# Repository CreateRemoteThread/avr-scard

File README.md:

# avr-scard

this is an extremely minimal t0 iso7816 reader based off an atmega328p, communicating over serial at 9600 baud.

this implements a fixed wait after 5 bytes of APDU, but otherwise does not guarantee reponses for APDU's. the pyserial driver is currently a part of [sparkgap](https://github.com/createremotethread/sparkgap). The pin out is as follows:

- B4: Status LED
- B0: Target I/O
- B2: Target Reset
- B1: Target Clk
- C5: Trigger (after APDU Send)

this is based off https://www.makomk.com/2011/02/25/iso-7816-smartcard-interface-for-arduino/

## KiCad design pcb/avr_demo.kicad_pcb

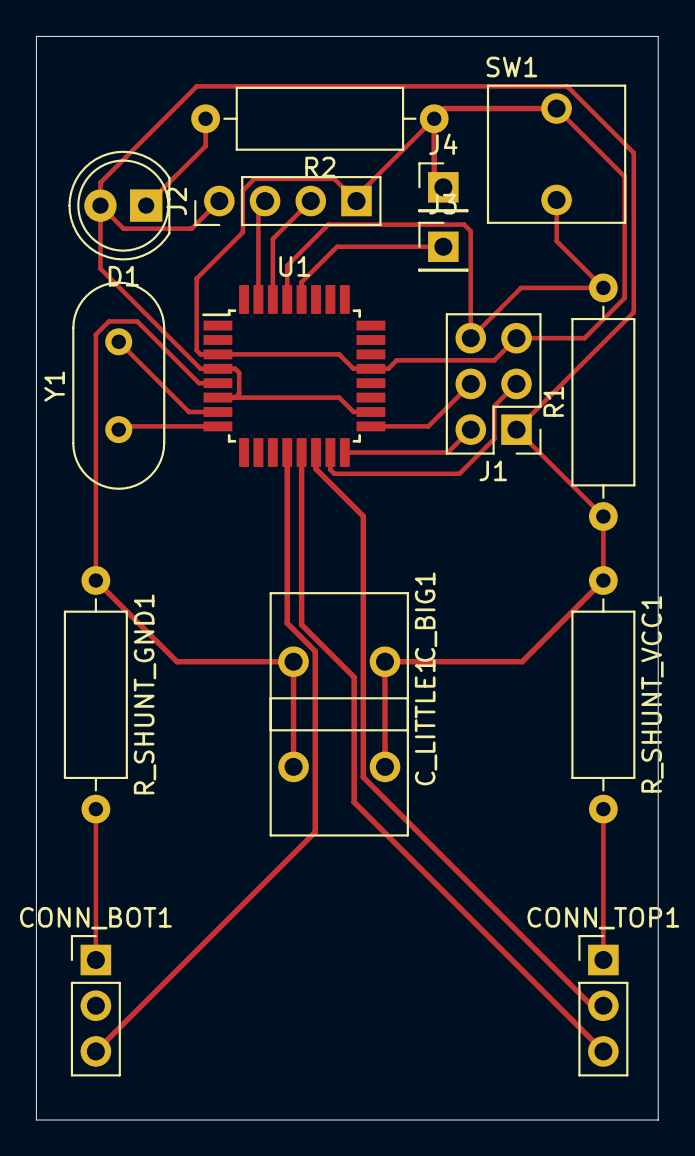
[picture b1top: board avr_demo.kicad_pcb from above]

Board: 2 copper layers, 34.5 x 60.2 mm, 16 parts (0 on the bottom side), 17 nets.

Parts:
CONN_BOT1: Conn_01x03; PinHeader_1x03_P2.54mm_Vertical
CONN_TOP1: Conn_01x03; PinHeader_1x03_P2.54mm_Vertical
C_BIG1: C; SW_6x6
C_LITTLE1: C; SW_6x6
D1: LED; LED_D5.0mm
J1: AVR-ISP-6; AVRISP_2x3
J2: Conn_01x04; PinHeader_1x04_P2.54mm_Vertical
J3, J4: Conn_01x01_Male; PinHeader_1x01_P2.54mm_Vertical
R1, R2: R; R_Axial_DIN0309_L9.0mm_D3.2mm_P12.70mm_Horizontal
R_SHUNT_GND1: R; R_Axial_DIN0309_L9.0mm_D3.2mm_P12.70mm_Horizontal
R_SHUNT_VCC1: R; R_Axial_DIN0309_L9.0mm_D3.2mm_P12.70mm_Horizontal
SW1: SW_Push; SW_6x6
U1: ATmega328P-AU; TQFP-32_7x7mm_P0.8mm
Y1: Crystal; Crystal_HC49-4H_Vertical

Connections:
GND: C_BIG1.2, C_LITTLE1.2, J1.6, J2.4, J4.1, R2.1, R_SHUNT_GND1.1, SW1.1, U1.3, U1.5, U1.21
ISP_MISO: J1.1, U1.16
ISP_MOSI: J1.4, U1.15
ISP_RST: J1.5, R1.2, SW1.2, U1.29
ISP_SCK: J1.3, U1.17
unnamed: CONN_BOT1.1, R_SHUNT_GND1.2
unnamed: CONN_TOP1.1, R_SHUNT_VCC1.2
unnamed: D1.1, R2.2
unnamed: U1.7, Y1.2
unnamed: U1.8, Y1.1
SC_CLK: CONN_TOP1.3, U1.13
SC_DATA: CONN_BOT1.3, U1.12
SC_RST: CONN_TOP1.2, U1.14
SC_TRIG: J3.1, U1.28
USART_RX: J2.3, U1.30
USART_TX: J2.2, U1.31
VCC: C_BIG1.1, C_LITTLE1.1, D1.2, J1.2, J2.1, R1.1, R_SHUNT_VCC1.1, U1.4, U1.6, U1.18

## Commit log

2020-05-13 asdf
    asdf
2020-05-13 documentation lol
    fkn lol
2020-05-17 fdg
    sdgf
2020-05-24 delay_us / delay_ms fixes
